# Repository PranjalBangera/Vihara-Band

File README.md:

# VIHARA BAND
### Smart Wearable for Motion Monitoring, Step Counting & Fall Detection

<p align="center">
  <strong>Embedded Systems | TinyML | Bluetooth Low Energy | PCB Design | Mobile Application</strong>
</p>

Vihara Band is an embedded wearable prototype developed during an industrial internship at **Zilliot Technologies**. The project combines motion sensing, embedded signal processing, step counting, fall-event analysis using TinyML, Bluetooth Low Energy (BLE) communication, and a companion application.

The system is designed to monitor everyday physical activity and identify potential fall events, with the aim of providing useful activity information and an alert pathway through a connected device.

---

## Table of Contents

- [Project Overview](#project-overview)
- [Key Features](#key-features)
- [System Architecture](#system-architecture)
- [Hardware Components](#hardware-components)
- [Embedded Firmware](#embedded-firmware)
- [Step Counting Algorithm](#step-counting-algorithm)
- [Fall Detection Using TinyML](#fall-detection-using-tinyml)
- [Bluetooth Low Energy Communication](#bluetooth-low-energy-communication)
- [Companion Application](#companion-application)
- [PCB Design](#pcb-design)
- [Repository Structure](#repository-structure)
- [Software and Tools](#software-and-tools)
- [Getting Started](#getting-started)
- [Testing and Verification](#testing-and-verification)
- [Current Development Status](#current-development-status)
- [Future Improvements](#future-improvements)
- [Learning Outcomes](#learning-outcomes)
- [Project Information](#project-information)

---

## Project Overview

Wearable motion-monitoring devices can help users understand their daily activity and identify unusual movement patterns. However, accelerometer data contains normal body movement, wrist rotation, sudden impacts and other signals that can lead to incorrect step counts or false fall alerts.

Vihara Band addresses these challenges through two separate processing approaches:

1. **Deterministic step counting:** Uses acceleration magnitude, digital filtering, threshold hysteresis and cadence verification to identify walking steps.
2. **Fall-event analysis:** Uses a multi-stage event-detection pipeline, motion features and a compact TinyML classifier to distinguish potential falls from ordinary activities.

The wearable uses a Silicon Labs EFR32BG22 Bluetooth Low Energy microcontroller and a Bosch BMA400 three-axis accelerometer. Activity and event information can be transmitted to a companion application through BLE.

### Project Objectives

- Develop an embedded wearable motion-monitoring system.
- Acquire and process three-axis accelerometer data.
- Implement reliable step-counting logic.
- Estimate distance and active minutes from activity data.
- Develop a multi-stage fall-detection pipeline using TinyML.
- Communicate activity and event information through BLE.
- Design a compact wearable PCB.
- Develop a companion application for displaying activity information and handling alerts.

---

## Key Features

| Feature | Description |
|---|---|
| Motion monitoring | Three-axis acceleration sensing using BMA400 |
| Step counting | Filtered acceleration and cadence-based verification |
| Distance estimation | Estimated from accumulated steps and configured stride length |
| Active minutes | Activity-duration tracking |
| Fall analysis | Freefall-like event, impact, stillness and TinyML classification |
| Manual SOS | Hardware event path for a manual SOS trigger |
| BLE communication | Wireless transfer of step and event information |
| Data persistence | Step-count storage using Silicon Labs NVM3 |
| Companion application | Activity dashboard and connected-device interface |
| PCB development | Custom wearable hardware design using KiCad |

---

## System Architecture

The system is divided into four major sections:

- **Sensing layer:** Captures motion data using the BMA400 accelerometer.
- **Processing layer:** Performs filtering, step counting and fall-event analysis on the EFR32BG22.
- **Communication layer:** Transfers activity and event information through BLE GATT.
- **Application layer:** Displays information and provides user-facing features through the companion application.

```text
              VIHARA BAND WEARABLE
                      |
                      v
             Bosch BMA400 Sensor
              3-Axis Accelerometer
                      |
                      v
             I2C Sensor Interface
                      |
                      v
             Silicon Labs EFR32BG22
                      |
             +--------+---------+
             |                  |
             v                  v
       Step Counting       Fall Detection
       Signal Filtering    Event State Machine
       Cadence Checks      Feature Extraction
                           TinyML Classifier
             |                  |
             +--------+---------+
                      |
                      v
               BLE GATT Service
                      |
                      v
              Android / Web App
                      |
             +--------+---------+
             |                  |
             v                  v
        Activity Dashboard   Fall / SOS Alerts
```

---

## Hardware Components

The hardware design combines motion sensing, wireless communication, power management, external memory and debugging interfaces.

| Component | Purpose |
|---|---|
| Silicon Labs EFR32BG22 | Main BLE microcontroller and embedded processing unit |
| Bosch BMA400 | Three-axis MEMS accelerometer |
| IS25LP064A | External SPI Flash memory |
| MCP73831 | Single-cell Li-ion battery charging controller |
| TLV73330 | 3.0 V low-dropout regulator |
| 2.4 GHz antenna | BLE wireless communication |
| RGB LED | Visual status indication |
| SWD connector | Programming and debugging |

### Important Hardware Configuration

| Parameter | Documented configuration |
|---|---|
| Motion sensor | Bosch BMA400 |
| Sensor sampling rate | 100 Hz |
| Acceleration range | ±8g |
| Communication interface | I2C |
| I2C clock speed | 100 kbit/s |
| BMA400 address | 0x15 default; startup probes 0x14/0x15 |
| Wireless communication | Bluetooth Low Energy |
| Supply rail | 3.0 V |

*These values describe the documented project configuration. Actual hardware operation should be confirmed during board bring-up.*

---

## Embedded Firmware

The firmware is developed in **Embedded C** for the Silicon Labs EFR32BG22 platform.

It handles sensor initialization, motion acquisition, activity processing, fall-event analysis, BLE communication and non-volatile data storage.

### Main Firmware Responsibilities

- Initialize the microcontroller and required peripherals.
- Communicate with the BMA400 accelerometer through I2C.
- Acquire and process acceleration data.
- Calculate acceleration magnitude.
- Perform step detection and cadence verification.
- Estimate activity-related parameters.
- Run the fall-detection state machine and TinyML inference.
- Publish activity and event information over BLE.
- Store step-count information using NVM3.
- Handle sensor communication errors and device status.

### Important Firmware Files

| File | Purpose |
|---|---|
| `app.c` | Main application logic |
| `app.h` | Application declarations |
| `app_ble.c` | BLE communication functionality |
| `app_ble.h` | BLE declarations |
| `main.c` | Firmware entry point |
| `fall_model.h` | Generated TinyML model representation |
| `VIHARA_BAND.slcp` | Silicon Labs project configuration |
| `BLE_SETUP.md` | BLE setup and testing notes |
| `config/btconf/gatt_configuration.btconf` | BLE GATT configuration |

---

## Step Counting Algorithm

The step-counting module uses filtered acceleration magnitude rather than treating every acceleration threshold crossing as a valid step.

### Processing Flow

1. Read the three-axis acceleration values.
2. Calculate the acceleration magnitude.
3. Apply exponential moving average filtering.
4. Detect a candidate step using an upper threshold.
5. Apply a minimum time interval between candidates.
6. Re-arm detection using a lower threshold.
7. Confirm a group of candidates within a time window.
8. Update the total step count.

### Documented Algorithm Parameters

| Parameter | Value |
|---|---:|
| EMA coefficient | 0.3 |
| Upper step threshold | 10.7 m/s² |
| Lower step threshold | 9.2 m/s² |
| Minimum step interval | 280 ms |
| Cadence confirmation | 3 candidates within 1.6 seconds |

The use of separate upper and lower thresholds introduces hysteresis, helping reduce repeated detections caused by noisy acceleration signals.

The confirmed step total is used for distance estimation and activity tracking. Step-count persistence is handled through NVM3 with batched writes.

---

## Fall Detection Using TinyML

Fall detection is implemented as a multi-stage analysis pipeline rather than relying on a single high-acceleration threshold.

A sudden impact can occur during ordinary activities such as running, jumping, dropping an object or hitting a surface. Therefore, the system checks the sequence of motion events before classifying a potential fall.

### Fall Detection Pipeline

```text
       Accelerometer Data
               |
               v
       Freefall-Like Event
               |
               v
         Impact Detection
               |
               v
        Post-Impact Stillness
               |
               v
        Feature Extraction
               |
               v
       TinyML Classification
               |
               v
        Fall Event Decision
               |
               v
          BLE Notification
```

### Documented Detection Parameters

| Parameter | Value |
|---|---:|
| Freefall threshold | Below 6.2 m/s² |
| Minimum freefall duration | 80 ms |
| Impact threshold | At least 21.5 m/s² |
| Stillness evaluation | At least 1,000 ms |
| Movement timeout | 1,500 ms |
| Classifier | Three-tree ensemble |
| Maximum tree depth | 4 |
| Classification method | Majority voting |

### TinyML Model

The fall-analysis pipeline extracts five motion features and uses a compact three-tree ensemble classifier.

The model is designed for resource-constrained embedded hardware, reducing the need for a large external processing system.

The physical event sequence gates the classification process, helping distinguish potential fall patterns from ordinary movement.

**Important:** The model and detection pipeline are prototype implementations. Their real-world sensitivity, specificity and false-alarm rate require systematic testing with labeled data.

---

## Bluetooth Low Energy Communication

BLE is used to connect the wearable to the companion application.

The firmware exposes a custom GATT service containing characteristics for step information, fall events and device status.

### Custom GATT Configuration

| Attribute | UUID | Purpose |
|---|---|---|
| Custom service | `12340000-1234-1234-1234-123456789012` | Vihara Band service |
| Step characteristic | `12340001-1234-1234-1234-123456789012` | Step-count information |
| Fall characteristic | `12340002-1234-1234-1234-123456789012` | Fall-event information |
| Status characteristic | `12340003-1234-1234-1234-123456789012` | Device status information |

### Documented BLE Configuration

- Advertising interval: 500 ms.
- Requested connection interval: 30–60 ms.
- Step-count payload: 3-byte little-endian unsigned integer.
- Fall-event codes:
  - `0x01` – Fall event.
  - `0x02` – Freefall warning.
  - `0x03` – Manual SOS.

BLE notifications allow the connected client to receive updates from the wearable.

---

## Companion Application

The companion application provides the user-facing interface for the Vihara Band system.

It includes a web-based application and an Android application wrapper using Capacitor.

### Technologies Used

| Technology | Purpose |
|---|---|
| HTML5 | Application structure |
| CSS3 | User interface styling |
| JavaScript ES6+ | Application functionality |
| Vite | Development server and build tool |
| Capacitor | Native Android integration |
| Bluetooth LE plugin | BLE scanning and communication |
| Firebase Authentication | Google sign-in integration |
| Capacitor Preferences | Local application preferences |

### Application Features

- User onboarding and guest access.
- Google sign-in integration.
- Activity dashboard and step goals.
- Activity rings and progress indicators.
- BMI calculation.
- BLE device scanning and connection.
- Signal-strength indication.
- Device reconnection handling.
- Step and fall-event telemetry parsing.
- Fall-alert interface with a cancellation countdown.
- Audio and haptic alert functionality.
- Emergency-contact selection and phone/SMS intent integration.
- Activity streaks, badges and weekly trends.
- CSV activity export.
- Progressive Web App support and offline service-worker functionality.

Emergency-contact and SOS-related application features should be treated as alert workflows, not proof that an emergency message has been successfully delivered.

---

## PCB Design

The Vihara Band hardware is being developed as a compact wearable PCB using **KiCad**.

The PCB design incorporates the microcontroller, motion sensor, power-management circuit, external Flash memory, BLE antenna network and programming/debugging connections.

### PCB Design Details

| Parameter | Detail |
|---|---|
| PCB design tool | KiCad |
| Board dimensions | 40.15 mm × 20 mm |
| Layer count | 4-layer |
| Board material | FR4 |
| Main controller | EFR32BG22 |
| Motion sensor | BMA400 |
| Wireless interface | 2.4 GHz BLE antenna and matching network |

### PCB Design Subsystems

- Microcontroller and BLE RF section.
- Accelerometer interface.
- Battery charging and power regulation.
- External SPI Flash.
- Programming and debugging interface.
- Status LED circuitry.
- Antenna and RF matching network.

**PCB development status:** The supplied design review identifies outstanding electrical and routing issues, including unconnected nets and RF, power and ground-plane concerns. The board should therefore be considered a work in progress, not a fabrication-ready design. DRC closure, routing review, antenna validation and hardware bring-up are required before manufacturing.

---

## Repository Structure

The repository brings together the firmware, application and PCB design resources.

```text
Vihara-Band/
│
├── README.md
│
├── Vihara-Band-main/
│   ├── app.c
│   ├── app.h
│   ├── app_ble.c
│   ├── app_ble.h
│   ├── main.c
│   ├── fall_model.h
│   ├── config/
│   ├── web/
│   ├── BLE_SETUP.md
│   └── VIHARA_BAND.slcp
│
├── Vihara-Band-Application-main/
│   ├── src/
│   │   ├── index.html
│   │   ├── js/
│   │   ├── css/
│   │   └── sw.js
│   ├── android/
│   ├── package.json
│   ├── capacitor.config.json
│   └── README.md
│
├── updated pcb/
│   ├── KiCad project files
│   ├── Schematic files
│   ├── PCB layout files
│   ├── BOM/
│   ├── Gerber exports/
│   └── Design review files/
│
├── Zilliot_Internship.pdf
│
└── LICENSE
```

*The structure above is a simplified overview of the main project areas. Individual files and subfolders may vary.*

---

## Software and Tools

| Tool / Platform | Usage |
|---|---|
| Silicon Labs Simplicity Studio 6 | Embedded firmware development |
| Silicon Labs Simplicity SDK | MCU and BLE development environment |
| Embedded C | Firmware programming |
| KiCad | Schematic and PCB design |
| Visual Studio Code | Application development |
| Node.js and npm | Application dependencies and build |
| Vite | Web application development |
| Capacitor | Android application integration |
| Firebase | Authentication integration |
| Git and GitHub | Version control and project documentation |

---

## Getting Started

### 1. Clone the Repository

```bash
git clone https://github.com/PranjalBangera/Vihara-Band.git
cd Vihara-Band
```

### 2. Embedded Firmware

1. Install Silicon Labs Simplicity Studio 6.
2. Install the compatible Silicon Labs Simplicity SDK.
3. Import or open the firmware project using its `.slcp` project configuration.
4. Check the target MCU and board configuration.
5. Verify the BMA400 I2C connection and peripheral configuration.
6. Build the firmware.
7. Flash the firmware to compatible hardware using the supported programming/debugging interface.

### 3. Companion Application

Open a terminal inside the application directory:

```bash
cd Vihara-Band-Application-main
```

Install dependencies:

```bash
npm install
```

Start the development server:

```bash
npm run dev
```

Create a production build:

```bash
npm run build
```

Synchronize the Capacitor Android project:

```bash
npx cap sync android
```

The Android project can then be opened in Android Studio for device-specific configuration and testing.

### 4. PCB Design

1. Install KiCad.
2. Open the supplied KiCad project.
3. Inspect the schematic and PCB layout.
4. Review the component footprints and board configuration.
5. Resolve electrical-rule and design-rule violations.
6. Complete routing and ground-plane verification.
7. Validate the antenna and power circuitry before fabrication.

---

## Testing and Verification

Testing is essential for evaluating step-count reliability, fall-detection behaviour, wireless communication and power consumption.

The project report identifies the following recommended verification activities:

| Test Area | Verification Approach |
|---|---|
| Sensor acquisition | Compare accelerometer readings with known orientations and inspect sample continuity |
| Step counting | Test slow, normal and fast walking and compare against manually counted steps |
| False step rejection | Test hand gestures, typing, desk taps and other everyday activities |
| Fall detection | Conduct supervised, cushioned simulations and record detected events |
| Activity rejection | Test running, jumping, clapping and dropped-device scenarios |
| Data persistence | Reboot after step-count updates and verify restored values |
| BLE communication | Test connections, notification subscriptions and reconnection |
| Power consumption | Measure current in sleep, sensing, advertising and connected modes |
| Application SOS | Verify permissions, alert states and actual delivery status using designated test contacts |

### Verification Metrics

For a labeled fall and activity dataset, useful evaluation metrics include:

- Sensitivity.
- Specificity.
- Precision.
- False alarms per hour or day.
- Missed-event rate.
- Step-count error.
- BLE notification latency.
- Recovery after disconnection.
- Battery current in different operating modes.

The supplied project materials describe the implementation and recommended tests, but do not establish a complete independently measured validation dataset, confusion matrix, whole-device battery-life result or verified emergency-message delivery.

---

## Current Development Status

| Project Area | Status |
|---|---|
| Embedded firmware | Implemented prototype |
| BMA400 sensor integration | Firmware support implemented; hardware verification required |
| Step counting | Algorithm implemented |
| Fall-event analysis | Multi-stage pipeline and TinyML model implemented |
| BLE communication | Custom GATT implementation |
| Companion application | Application implementation available |
| PCB design | Under development; design issues remain |
| Full system validation | Further testing required |

### Important Hardware Configuration Note

The supplied firmware configuration references `EFR32BG22C224F512IM40`, while the PCB BOM lists `EFR32BG22C224F512GM32-C`.

These part-number differences should be checked against the actual selected component, package, pinout and board design before firmware deployment or PCB fabrication.

---

## Future Improvements

1. Collect ethically approved real-world accelerometer data from different users and wearable placements.
2. Improve fall classification using subject-independent training and evaluation.
3. Measure sensitivity, specificity, precision and false alarms per unit time.
4. Calibrate step thresholds and stride length using measured walking sessions.
5. Verify sensor timing, interrupt handling and axis conversion on the actual board.
6. Measure BLE notification latency and reconnection reliability.
7. Improve application-side data validation and connection recovery.
8. Verify SOS delivery states and emergency-contact workflows.
9. Measure complete-device power consumption and estimate battery life using actual battery capacity.
10. Complete PCB routing, DRC checks, antenna tuning and hardware bring-up.
11. Add structured diagnostic logs, watchdog recovery and persistent-record validation.

---

## Learning Outcomes

This project provided practical exposure to several areas of electronics and embedded-system development:

- Embedded C programming.
- Silicon Labs EFR32BG22 microcontroller development.
- I2C-based sensor communication.
- Accelerometer data acquisition and signal processing.
- Digital filtering and threshold hysteresis.
- Step-counting algorithm development.
- State-machine-based event detection.
- TinyML model integration on embedded hardware.
- Bluetooth Low Energy advertising and GATT communication.
- Non-volatile memory management using NVM3.
- Schematic interpretation and PCB design using KiCad.
- RF layout and power-management considerations.
- Web and Android application development.
- System testing, debugging and technical documentation.

---

## Project Information

| Detail | Information |
|---|---|
| Project | Vihara Band |
| Organization | Zilliot Technologies |
| Programme | Advanced Communication Technology |
| Institution | NMAM Institute of Technology, Nitte |
| Year | 2026 |
| Project type | Industrial Internship / Embedded Systems Project |

### Project Team

- Avinash Shetty
- Pramith Suvarna
- Pranjal Bangera
- Jostan Saldanha

### Company Mentors

- Mr Puneeth Salian
- Mrs Supriya Naik

---

## Disclaimer

Vihara Band is an academic and engineering prototype developed for learning and demonstration purposes. It is not a certified medical device and must not be relied upon as a guaranteed fall-detection or emergency-response system. Real-world deployment requires extensive validation, safety assessment, hardware verification and reliable emergency communication testing.

---

<p align="center">
  <strong>Vihara Band — Connecting Embedded Intelligence with Wearable Technology.</strong>
</p>

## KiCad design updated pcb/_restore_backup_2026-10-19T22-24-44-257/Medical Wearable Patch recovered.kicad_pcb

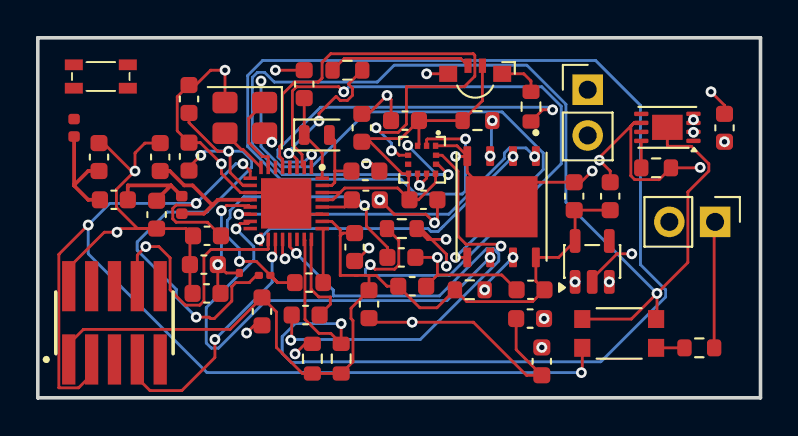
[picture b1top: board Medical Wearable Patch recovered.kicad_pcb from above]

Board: 4 copper layers, 40.2 x 20.0 mm, 54 parts (0 on the bottom side), 38 nets.

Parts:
ANT1: 2450AT18D0100E; Chip Antenna
C1, C3, C6, C12, C13, C17, C20, C27: 100nF; C_0603_1608Metric
C2, C9, C14, C19, C28: 1µF; C_0603_1608Metric
C4, C7: 120pF; C_0603_1608Metric
C5: 1.2pF; C_0603_1608Metric
C8: 18pF; C_0603_1608Metric
C10: 1.3pF; C_0603_1608Metric
C11: 1.5pF; C_0603_1608Metric
C15, C21, C29, C30: 4.7µF; C_0603_1608Metric
C16: 10nF; C_0603_1608Metric
C18: 10µF; C_0603_1608Metric
C25, C26: 18 pF; C_0603_1608Metric
D1: LED_RGBA; LED_Kingbright_APFA3010_3x1.5mm_Horizontal
IC2: EFR32BG22C224F512GM32-C
J2, J4: Conn_01x02; PinHeader_1x02_P2.54mm_Vertical
J5: FTSH-105-01-L-DV-K; SAMTEC_FTSH-105-01-L-DV-K
L1, L3: 742692004; L_0201_0603Metric
L2: 2.6nH; L_0402_1005Metric
L4: 1.5nH; L_0402_1005Metric
L5: 2.2µH; L_0603_1608Metric
R1, R3, R4, R8: 10kΩ; R_0603_1608Metric
R5, R6, R7: 330Ω; R_0603_1608Metric
R9, R10: 4.7kΩ; R_0603_1608Metric
SW1: SW_Push; SW_KMR211NGLFS
U1: BMA400; XDCR_BMA400
U2: MCP73831-2-MC; DFN-8-1EP_3x2mm_P0.5mm_EP1.7x1.4mm
U3: TLV73330PDBV; SOT-23-5
U5: IS25LP064A-JKLE-TR; SON127P500X600X80-9N
Y1: ABM8-38.400MHZ-10-B1U-T; Crystal_SMD_Abracon_ABM8G-4Pin_3.2x2.5mm
Y4: 32.768kHz; Crystal_SMD_2012-2Pin_2.0x1.2mm

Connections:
/BG22/3V: C1.1, C12.1, C14.1, C16.1, C17.1, C18.1, C19.1, C20.1, C27.1, C30.1, D1.4 (A), IC2.26 (VREGVDD), IC2.29 (AVDD), IC2.30 (IOVDD), J5.1, R3.1, R8.1, R9.1, R10.1, U1.3 (VDDIO), U1.7 (VDD), U1.10 (~CSB), U3.5 (OUT), U5.8 (VCC)
/BG22/Alert: IC2.5 (PC04), U1.5 (INT1)
/BG22/FLASH_CS: IC2.14 (PB02), U5.1 (~CE)
/BG22/FLASH_MISO: IC2.17 (PA00), U5.2 (SO(IO1))
/BG22/FLASH_MOSI: IC2.6 (PC05), U5.5 (SI(IO0))
/BG22/FLASH_SCK: IC2.15 (PB01), U5.6 (SCK)
/BG22/LED_B: IC2.3 (PC02), R7.2
/BG22/LED_G: IC2.2 (PC01), R5.2
/BG22/LED_R: IC2.1 (PC00), R6.2
/BG22/LFXO_IN: C25.1, IC2.32 (PD00), Y4.1
/BG22/LFXO_OUT: C26.1, IC2.31 (PD01), Y4.2
/BG22/PAVDD: C6.1, C7.1, IC2.13 (PAVDD), L3.1
/BG22/RF1: C8.2, C10.1, L2.1
/BG22/RF2: C10.2, C11.2, L4.2
/BG22/RF2G4_IO: C5.2, IC2.12 (RF2G4_IO), L2.2
/BG22/RF3: ANT1.4 (GND/FEED), L4.1
/BG22/RFVDD: C3.1, C4.1, IC2.10 (RFVDD), L1.2
/BG22/RST: C2.1, IC2.9 (RESETN), J5.3, SW1.2
/BG22/SCL: IC2.21 (PA04), R9.2, U1.12 (SCX)
/BG22/SDA: IC2.23 (PA06), R10.2, U1.2 (SDX)
/BG22/SWCLK: IC2.18 (PA01), J5.8
/BG22/SWDIO: IC2.19 (PA02), J5.7
/BG22/SWO: IC2.20 (PA03), J5.6
/BG22/VDCDC: C13.1, C15.1, IC2.28 (DVDD), L1.1, L3.2, L5.2
/BG22/VREGSW: IC2.25 (VREGSW), L5.1
/BG22/X1: IC2.7 (HFXTAL_I), Y1.1 (X1)
/BG22/X2: IC2.8 (HFXTAL_O), Y1.3 (X2)
/Power/5v: C28.1, J4.2, U2.1 (V_{DD}), U2.2 (V_{DD})
GND: ANT1.1 (FEED/GND), ANT1.2 (GND_1), ANT1.3 (GND_2), C1.2, C2.2, C3.2, C4.2, C5.1, C6.2, C7.2, C8.1, C9.2, C11.1, C12.2, C13.2, C14.2, C15.2, C16.2, C17.2, C18.2, C19.2, C20.2, C21.2, C25.2, C26.2, C27.2, C28.2, C29.2, C30.2, IC2.11 (RFVSS), IC2.27 (VREGVSS), IC2.33 (VSS), J2.2, J4.1, J5.2, R1.2, R4.1, U1.1 (SDO), U1.8 (GNDIO), U1.9 (GND), U2.6 (V_{SS}), U3.2 (GND), U5.4 (GND), U5.9 (EXP), Y1.2 (GND_1), Y1.4 (GND_2)
unnamed: D1.3 (BK), R7.1
unnamed: D1.2 (GK), R5.1
unnamed: D1.1 (RK), R6.1
unnamed: C9.1, IC2.24 (DECOUPLE)
unnamed: C21.1, C29.1, J2.1, U2.3 (V_{BAT}), U2.4 (V_{BAT}), U3.1 (IN), U3.3 (EN)
unnamed: R4.2, SW1.1
unnamed: R1.1, U2.8 (PROG)
unnamed: R8.2, U5.7 (~HOLD(IO3))
unnamed: R3.2, U5.3 (~WP(IO2))

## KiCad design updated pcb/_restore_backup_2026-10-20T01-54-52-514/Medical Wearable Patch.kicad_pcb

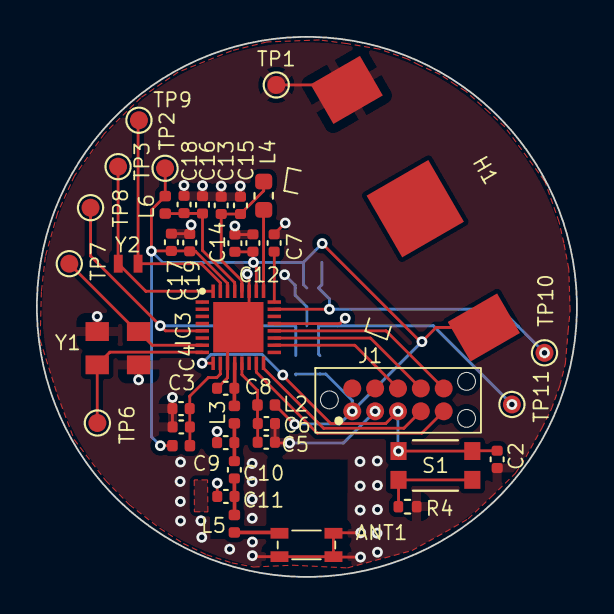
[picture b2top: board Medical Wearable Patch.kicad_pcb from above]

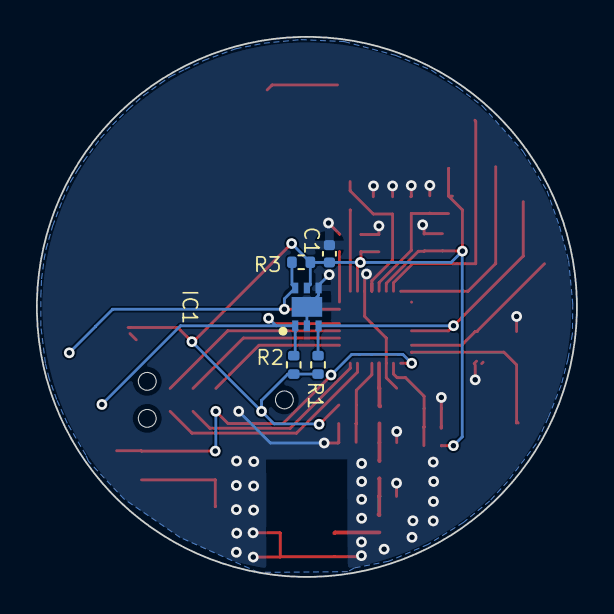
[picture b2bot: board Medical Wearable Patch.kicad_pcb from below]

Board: 2 copper layers, 30.0 x 30.0 mm, 46 parts (5 on the bottom side), 26 nets.

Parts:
ANT1: 2450AT18D0100E; Chip Antenna
C1: 100n; C_0402_1005Metric
C2: 0.1u; C_0402_1005Metric
C3, C5, C12, C15, C17: 100nF; C_0402_1005Metric
C4, C6: 120pF; C_0402_1005Metric
C7: 1u; C_0402_1005Metric
C8: 1.2pF; C_0402_1005Metric
C9: 1.3pF; C_0402_1005Metric
C10: 18pF; C_0402_1005Metric
C11: 1pF; C_0402_1005Metric
C13: 4.7uF; C_0402_1005Metric
C14, C18: 10uF; C_0402_1005Metric
C16: 10nF; C_0402_1005Metric
C19: 1uF; C_0402_1005Metric
H1: 2894; CR1220
IC1: TMP117MAIDRVR
IC3: EFR32BG22C224F512GM32-C
J1: Conn_02x05_Odd_Even; Tag Connect - 10 Pin
L1, L2, L6: L; L_0402_1005Metric
L3: 2.6nH; L_0402_1005Metric
L4: 2.2uH; L_0603_1608Metric
L5: 1.5nH; L_0402_1005Metric
R1, R2, R3: 5K; R_0402_1005Metric
R4: 100R; R_0402_1005Metric
S1: KMR211NGLFS; SW_KMR211NGLFS
TP1: GND; TestPoint_Pad_D1.0mm
TP2: 3V; TestPoint_Pad_D1.0mm
TP3: Alert; TestPoint_Pad_D1.0mm
TP6: HFXO_O; TestPoint_Pad_D1.0mm
TP7: HFXO_I; TestPoint_Pad_D1.0mm
TP8: LFXO_O; TestPoint_Pad_D1.0mm
TP9: LFXO_I; TestPoint_Pad_D1.0mm
TP10: SDA; TestPoint_Pad_D1.0mm
TP11: SCL; TestPoint_Pad_D1.0mm
Y1: ABM8-38.400MHZ-10-B1U-T; 38.4MHz Crystal
Y2: FC1610AN_32.7680KA-AG; 32.768kHz_LFXO

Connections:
/BG22/3V: C1.1, C12.1, C14.1, C17.1, C19.1, H1.1 (+), IC1.5 (V+), IC3.26 (VREGVDD), IC3.30 (IOVDD), J1.1, L1.1, L2.2, L6.2, R1.1, R2.1, R3.1, TP2.1
/BG22/AVDD: C16.1, C18.1, IC3.29 (AVDD), L6.1
/BG22/Alert: IC1.3 (ALERT), IC3.5 (PC04), R1.2, TP3.1
/BG22/PD0: IC3.32 (PD00), TP8.1, Y2.1
/BG22/PD1: IC3.31 (PD01), TP9.1, Y2.2
/BG22/RF1: C9.2, C10.1, L3.1
/BG22/RF2: C10.2, C11.2, L5.2
/BG22/RF2G4_IO: C8.2, IC3.12 (RF2G4_IO), L3.2
/BG22/RF3: ANT1.4 (GND/FEED), L5.1
/BG22/RST: C2.1, IC3.9 (RESETN), J1.3, S1.1, S1.2
/BG22/SCL: IC1.1 (SCL), IC3.21 (PA04), R2.2, TP11.1
/BG22/SDA: IC1.6 (SDA), IC3.23 (PA06), R3.2, TP10.1
/BG22/SWCLK: IC3.18 (PA01), J1.8
/BG22/SWDIO: IC3.19 (PA02), J1.7
/BG22/SWO: IC3.20 (PA03), J1.6
/BG22/UART_Rx: IC3.16 (PB00), J1.4
/BG22/UART_Tx: IC3.15 (PB01), J1.5
/BG22/VDCDC: C13.1, C15.1, IC3.28 (DVDD), L4.2
/BG22/VREGSW: IC3.25 (VREGSW), L4.1
/BG22/X1: IC3.7 (HFXTAL_I), TP7.1, Y1.1 (X1)
/BG22/X2: IC3.8 (HFXTAL_O), TP6.1, Y1.3 (X2)
GND: ANT1.1 (FEED/GND), ANT1.2 (GND_1), ANT1.3 (GND_2), C1.2, C2.2, C3.2, C4.2, C5.2, C6.2, C7.2, C8.1, C9.1, C11.1, C12.2, C13.2, C14.2, C15.2, C16.2, C17.2, C18.2, C19.2, H1.2 (-), IC1.2 (GND), IC1.4 (ADD0), IC1.7 (EP), IC3.11 (RFVSS), IC3.27 (VREGVSS), IC3.33 (VSS), J1.2, R4.1, TP1.1, Y1.2 (GND_1), Y1.4 (GND_2)
unnamed: C7.1, IC3.24 (DECOUPLE)
unnamed: C5.1, C6.1, IC3.13 (PAVDD), L2.1
unnamed: C3.1, C4.1, IC3.10 (RFVDD), L1.2
unnamed: R4.2, S1.3, S1.4
